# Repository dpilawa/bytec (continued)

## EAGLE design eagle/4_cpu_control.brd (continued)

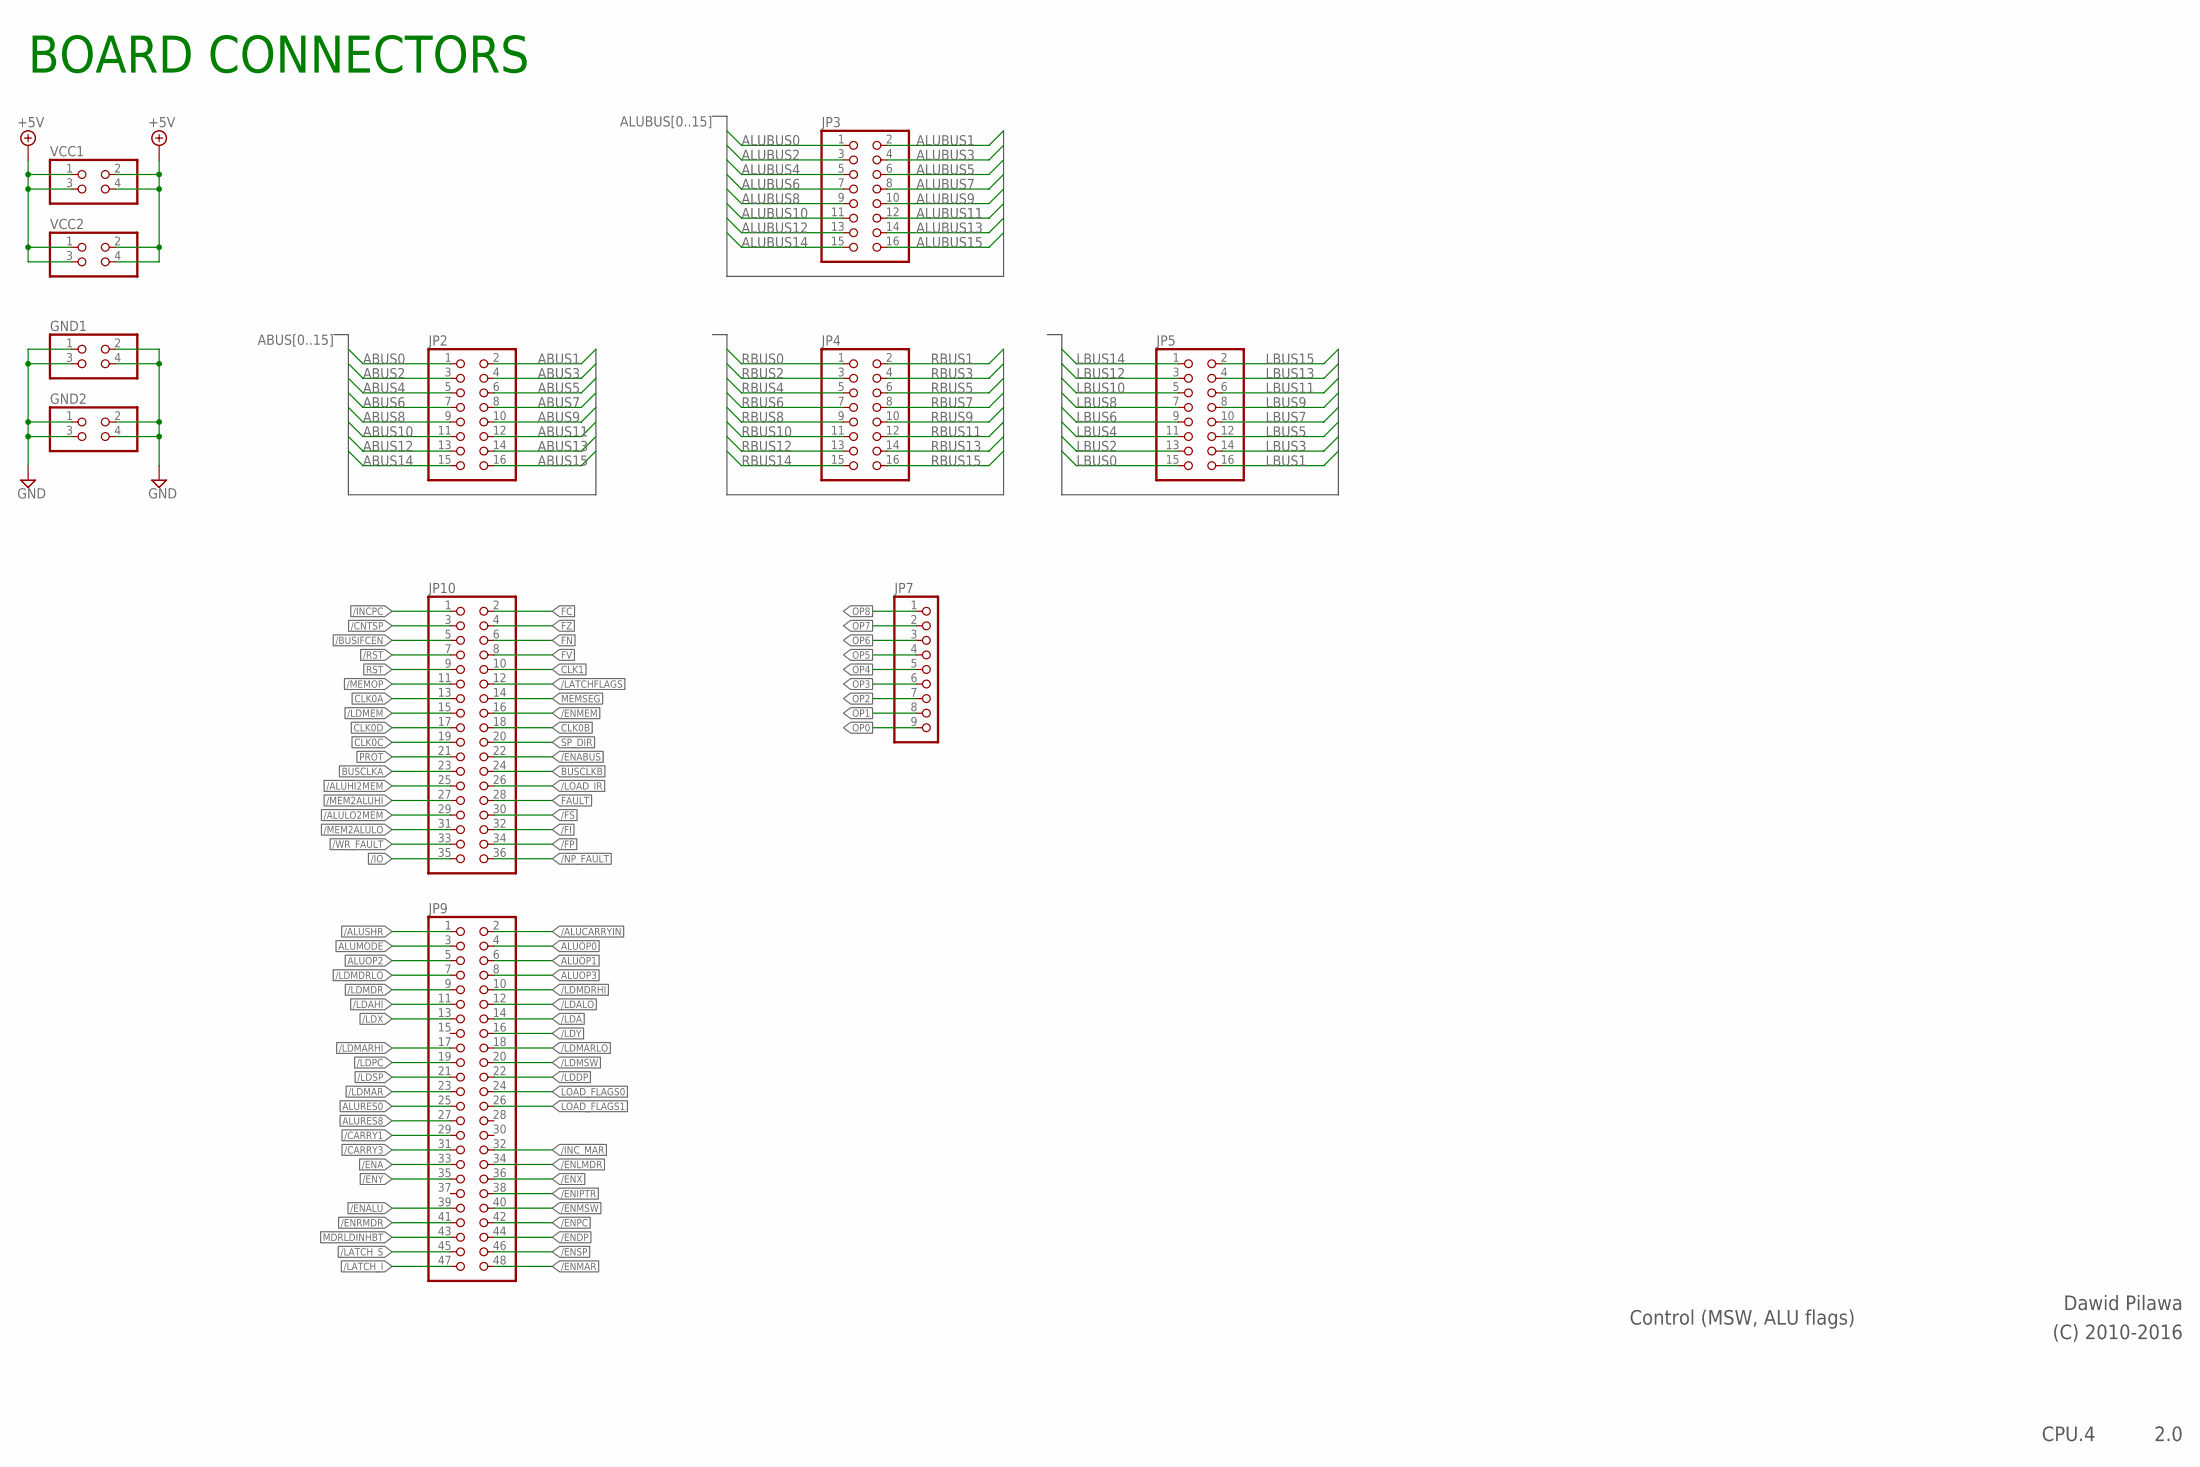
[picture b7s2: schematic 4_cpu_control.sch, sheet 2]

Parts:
GND1, GND2: PINHD-2X2; 2X02
JP2, JP3, JP4, JP5: PINHD-2X8; 2X08
JP7: PINHD-1X9; 1X09
JP9: PINHD-2X24; 2X24
JP10: PINHD-2X18; 2X18
VCC1, VCC2: PINHD-2X2; 2X02

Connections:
+5V: VCC1.1, VCC1.2, VCC1.3, VCC1.4, VCC2.1, VCC2.2, VCC2.3, VCC2.4; also elsewhere on the board
/ALUCARRYIN: JP9.2
/ALUHI2MEM: JP10.25
/ALULO2MEM: JP10.29
/ALUSHR: JP9.1; also elsewhere on the board
/BUSIFCEN: JP10.5
/CARRY1: JP9.29; also elsewhere on the board
/CARRY3: JP9.31; also elsewhere on the board
/CNTSP: JP10.3
/ENA: JP9.33
/ENABUS: JP10.22
/ENALU: JP9.39
/ENDP: JP9.44
/ENIPTR: JP9.38; also elsewhere on the board
/ENLMDR: JP9.34
/ENMAR: JP9.48
/ENMEM: JP10.16
/ENMSW: JP9.40; also elsewhere on the board
/ENPC: JP9.42
/ENRMDR: JP9.41
/ENSP: JP9.46
/ENX: JP9.36
/ENY: JP9.35
/FI: JP10.32; also elsewhere on the board
/FP: JP10.34; also elsewhere on the board
/FS: JP10.30; also elsewhere on the board
/INCPC: JP10.1
/INC_MAR: JP9.32
/IO: JP10.35
/LATCHFLAGS: JP10.12
/LATCH_I: JP9.47; also elsewhere on the board
/LATCH_S: JP9.45; also elsewhere on the board
/LDA: JP9.14
/LDAHI: JP9.11
/LDALO: JP9.12
/LDDP: JP9.22
/LDMAR: JP9.23
/LDMARHI: JP9.17
/LDMARLO: JP9.18
/LDMDR: JP9.9
/LDMDRHI: JP9.10
/LDMDRLO: JP9.7
/LDMEM: JP10.15
/LDMSW: JP9.20; also elsewhere on the board
/LDPC: JP9.19
/LDSP: JP9.21
/LDX: JP9.13
/LDY: JP9.16
/LOAD_IR: JP10.26
/MEM2ALUHI: JP10.27
/MEM2ALULO: JP10.31
/MEMOP: JP10.11
/NP_FAULT: JP10.36
/RST: JP10.7; also elsewhere on the board
/WR_FAULT: JP10.33
ABUS0: JP2.1
ABUS1: JP2.2
ABUS2: JP2.3
ABUS3: JP2.4
ABUS4: JP2.5
ABUS5: JP2.6
ABUS6: JP2.7
ABUS7: JP2.8
ABUS8: JP2.9
ABUS9: JP2.10
ABUS10: JP2.11
ABUS11: JP2.12
ABUS12: JP2.13
ABUS13: JP2.14
ABUS14: JP2.15
ABUS15: JP2.16
ALUBUS0: JP3.1; also elsewhere on the board
ALUBUS1: JP3.2; also elsewhere on the board
ALUBUS2: JP3.3; also elsewhere on the board
ALUBUS3: JP3.4; also elsewhere on the board
ALUBUS4: JP3.5; also elsewhere on the board
ALUBUS5: JP3.6; also elsewhere on the board
ALUBUS6: JP3.7; also elsewhere on the board
ALUBUS7: JP3.8; also elsewhere on the board
ALUBUS8: JP3.9; also elsewhere on the board
ALUBUS9: JP3.10; also elsewhere on the board
ALUBUS10: JP3.11; also elsewhere on the board
ALUBUS11: JP3.12; also elsewhere on the board
ALUBUS12: JP3.13; also elsewhere on the board
ALUBUS13: JP3.14; also elsewhere on the board
ALUBUS14: JP3.15; also elsewhere on the board
ALUBUS15: JP3.16; also elsewhere on the board
ALUMODE: JP9.3
ALUOP0: JP9.4
ALUOP1: JP9.6; also elsewhere on the board
ALUOP2: JP9.5
ALUOP3: JP9.8
ALURES0: JP9.25; also elsewhere on the board
ALURES8: JP9.27; also elsewhere on the board
BUSCLKA: JP10.23
BUSCLKB: JP10.24; also elsewhere on the board
CLK0A: JP10.13
CLK0B: JP10.18
CLK0C: JP10.19
CLK0D: JP10.17; also elsewhere on the board
CLK1: JP10.10
FAULT: JP10.28
FC: JP10.2; also elsewhere on the board
FN: JP10.6; also elsewhere on the board
FV: JP10.8; also elsewhere on the board
FZ: JP10.4; also elsewhere on the board
GND: GND1.1, GND1.2, GND1.3, GND1.4, GND2.1, GND2.2, GND2.3, GND2.4; also elsewhere on the board
LBUS0: JP5.15
LBUS1: JP5.16
LBUS2: JP5.13
LBUS3: JP5.14
LBUS4: JP5.11
LBUS5: JP5.12
LBUS6: JP5.9
LBUS7: JP5.10; also elsewhere on the board
LBUS8: JP5.7
LBUS9: JP5.8
LBUS10: JP5.5
LBUS11: JP5.6
LBUS12: JP5.3
LBUS13: JP5.4
LBUS14: JP5.1
LBUS15: JP5.2; also elsewhere on the board
LOAD_FLAGS0: JP9.24; also elsewhere on the board
LOAD_FLAGS1: JP9.26; also elsewhere on the board
MDRLDINHBT: JP9.43
MEMSEG: JP10.14
OP0: JP7.9; also elsewhere on the board
OP1: JP7.8; also elsewhere on the board
OP2: JP7.7; also elsewhere on the board
OP3: JP7.6; also elsewhere on the board
OP4: JP7.5
OP5: JP7.4
OP6: JP7.3
OP7: JP7.2
OP8: JP7.1
PROT: JP10.21
RBUS0: JP4.1; also elsewhere on the board
RBUS1: JP4.2; also elsewhere on the board
RBUS2: JP4.3; also elsewhere on the board
RBUS3: JP4.4; also elsewhere on the board
RBUS4: JP4.5; also elsewhere on the board
RBUS5: JP4.6; also elsewhere on the board
RBUS6: JP4.7; also elsewhere on the board
RBUS7: JP4.8; also elsewhere on the board
RBUS8: JP4.9; also elsewhere on the board
RBUS9: JP4.10; also elsewhere on the board
RBUS10: JP4.11; also elsewhere on the board
RBUS11: JP4.12; also elsewhere on the board
RBUS12: JP4.13; also elsewhere on the board
RBUS13: JP4.14; also elsewhere on the board
RBUS14: JP4.15; also elsewhere on the board
RBUS15: JP4.16; also elsewhere on the board
RST: JP10.9; also elsewhere on the board
SP_DIR: JP10.20

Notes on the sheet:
Control (MSW, ALU flags)
2.0
Dawid Pilawa
(C) 2010-2016
CPU.4
BOARD CONNECTORS

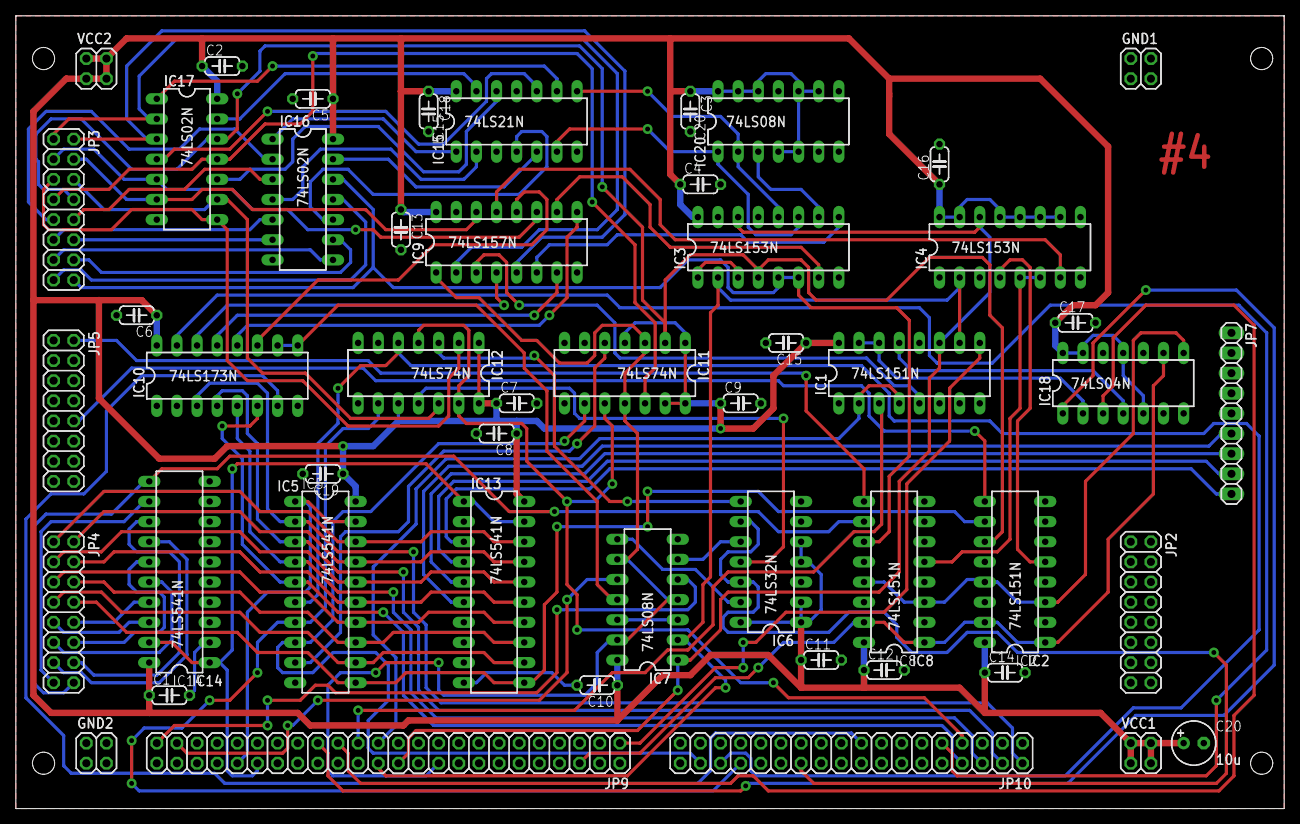
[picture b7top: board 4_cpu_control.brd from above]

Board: 2 copper layers, 160.0 x 100.0 mm, 50 parts (0 on the bottom side), 95 nets.

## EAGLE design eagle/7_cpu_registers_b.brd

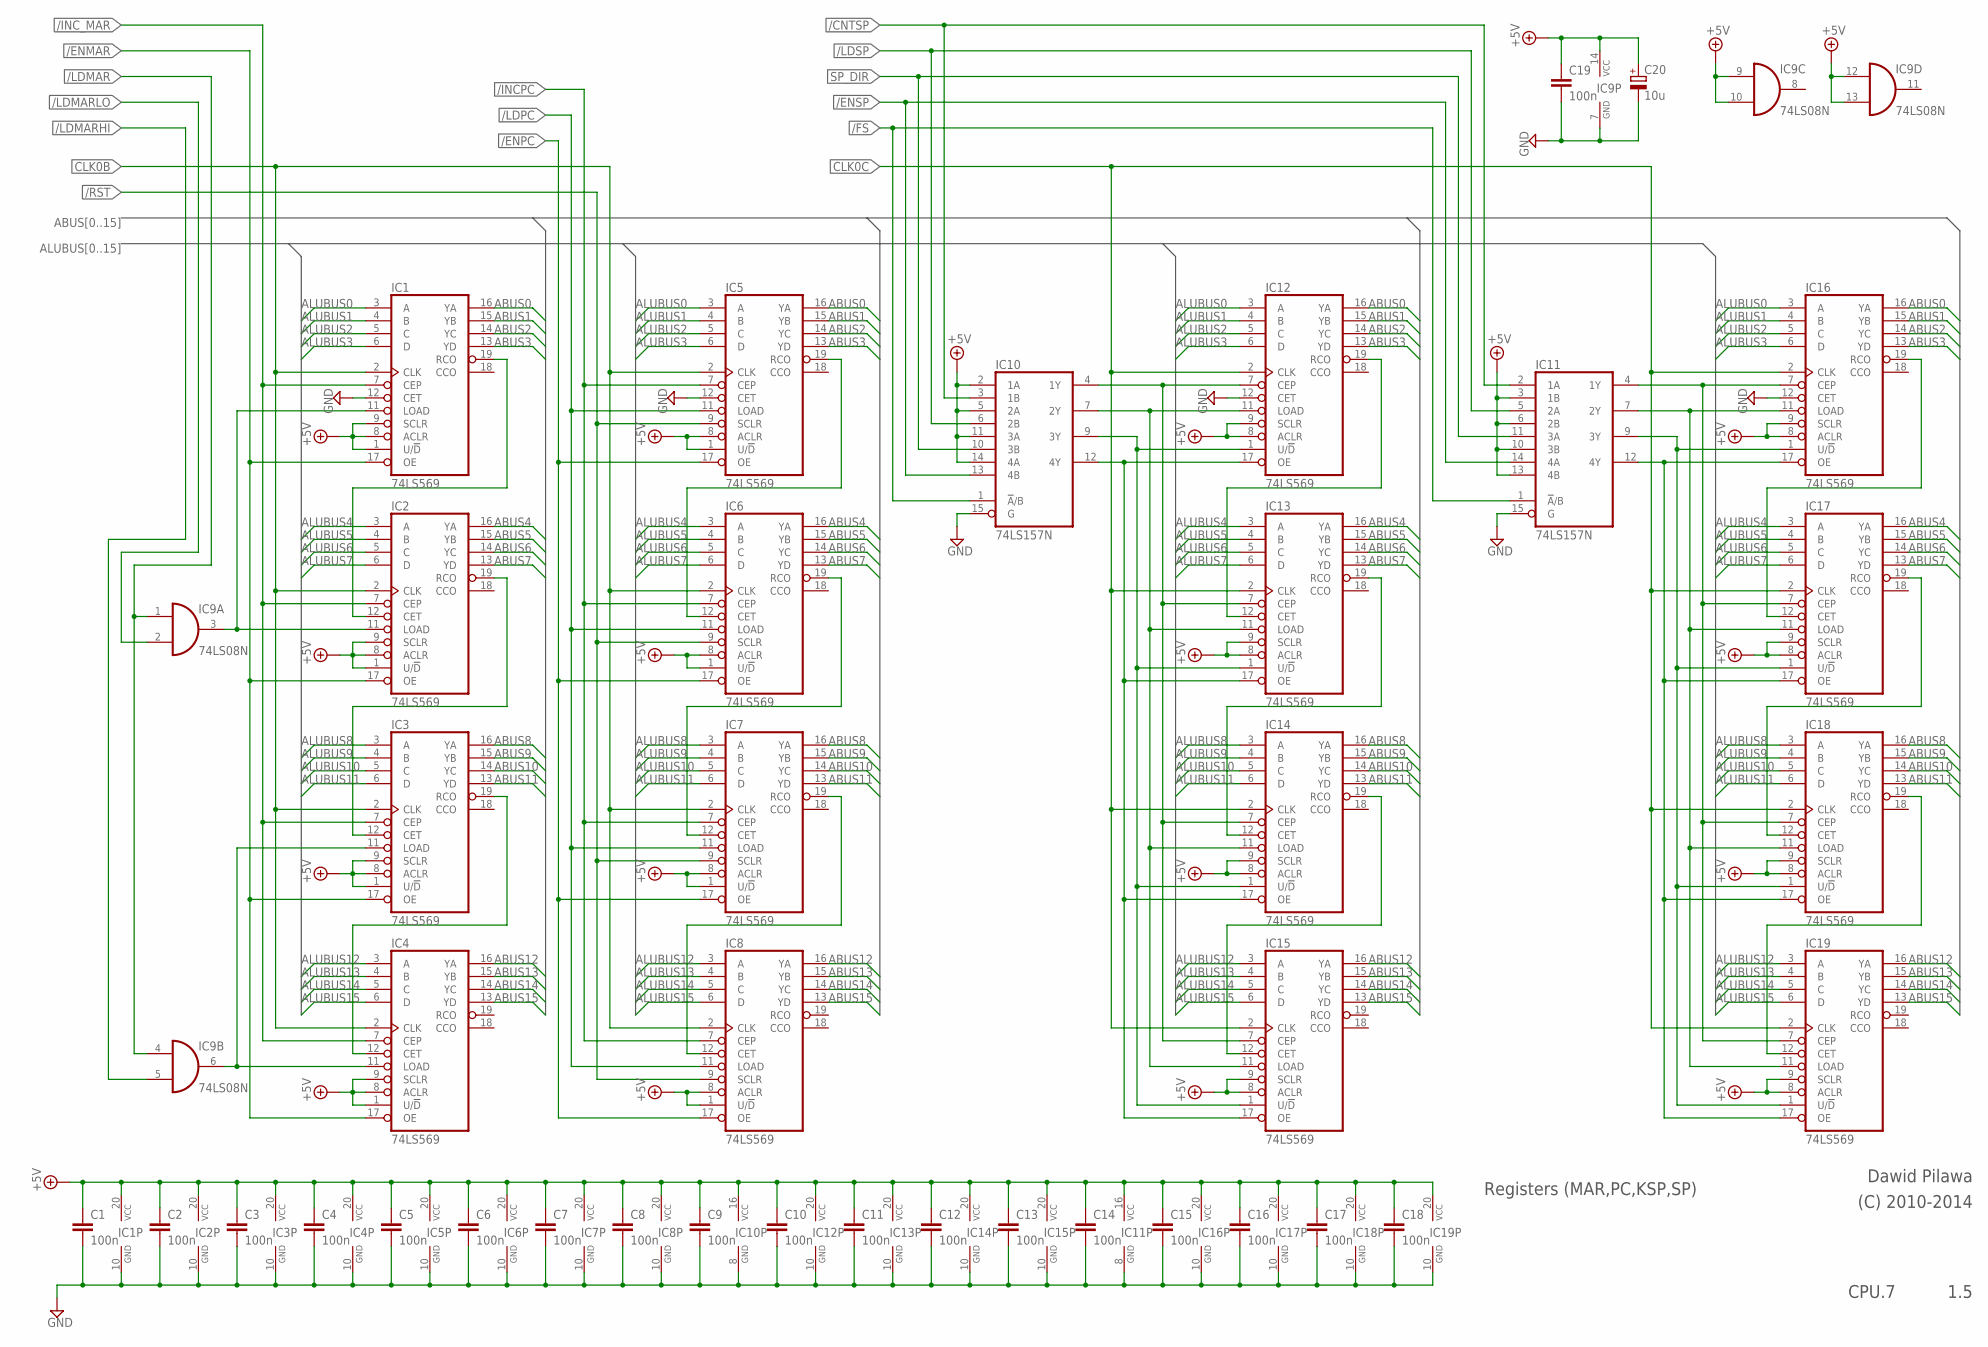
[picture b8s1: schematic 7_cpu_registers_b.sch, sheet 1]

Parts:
C1, C2, C3, C4, C5, C6, C7, C8, C9, C10, C11, C12, C13, C14, C15, C16, C17, C18, C19: 100n; C050-024X044
C20: 10u; E2,5-6
IC1, IC2, IC3, IC4, IC5, IC6, IC7, IC8, IC12, IC13, IC14, IC15, IC16, IC17, IC18, IC19: 74LS569; DIL20
IC9: 74LS08N; DIL14
IC10, IC11: 74LS157N; DIL16

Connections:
+5V: C1.1, C2.1, C3.1, C4.1, C5.1, C6.1, C7.1, C8.1, C9.1, C10.1, C11.1, C12.1, C13.1, C14.1, C15.1, C16.1, C17.1, C18.1, C19.1, C20.+, IC1.1 (U/!D), IC1.8 (ACLR), IC1.9 (SCLR), IC1.20 (VCC), IC2.1 (U/!D), IC2.8 (ACLR), IC2.9 (SCLR), IC2.20 (VCC), IC3.1 (U/!D), IC3.8 (ACLR), IC3.9 (SCLR), IC3.20 (VCC), IC4.1 (U/!D), IC4.8 (ACLR), IC4.9 (SCLR), IC4.20 (VCC), IC5.1 (U/!D), IC5.8 (ACLR), IC5.20 (VCC), IC6.1 (U/!D), IC6.8 (ACLR), IC6.20 (VCC), IC7.1 (U/!D), IC7.8 (ACLR), IC7.20 (VCC), IC8.1 (U/!D), IC8.8 (ACLR), IC8.20 (VCC), IC9.9 (I0), IC9.10 (I1), IC9.12 (I0), IC9.13 (I1), IC9.14 (VCC), IC10.2 (1A), IC10.5 (2A), IC10.11 (3A), IC10.14 (4A), IC10.16 (VCC), IC11.3 (1B), IC11.6 (2B), IC11.10 (3B), IC11.13 (4B), IC11.16 (VCC), IC12.8 (ACLR), IC12.9 (SCLR), IC12.20 (VCC), IC13.8 (ACLR), IC13.9 (SCLR), IC13.20 (VCC), IC14.8 (ACLR), IC14.9 (SCLR), IC14.20 (VCC), IC15.8 (ACLR), IC15.9 (SCLR), IC15.20 (VCC), IC16.8 (ACLR), IC16.9 (SCLR), IC16.20 (VCC), IC17.8 (ACLR), IC17.9 (SCLR), IC17.20 (VCC), IC18.8 (ACLR), IC18.9 (SCLR), IC18.20 (VCC), IC19.8 (ACLR), IC19.9 (SCLR), IC19.20 (VCC); also elsewhere on the board
/CNTSP: IC10.3 (1B), IC11.2 (1A); also elsewhere on the board
/ENMAR: IC1.17 (OE), IC2.17 (OE), IC3.17 (OE), IC4.17 (OE); also elsewhere on the board
/ENPC: IC5.17 (OE), IC6.17 (OE), IC7.17 (OE), IC8.17 (OE); also elsewhere on the board
/ENSP: IC10.13 (4B), IC11.14 (4A); also elsewhere on the board
/FS: IC10.1 (!A!/B), IC11.1 (!A!/B); also elsewhere on the board
/INCPC: IC5.7 (CEP), IC6.7 (CEP), IC7.7 (CEP), IC8.7 (CEP); also elsewhere on the board
/INC_MAR: IC1.7 (CEP), IC2.7 (CEP), IC3.7 (CEP), IC4.7 (CEP); also elsewhere on the board
/LDMAR: IC9.1 (I0), IC9.4 (I0); also elsewhere on the board
/LDMARHI: IC9.5 (I1); also elsewhere on the board
/LDMARLO: IC9.2 (I1); also elsewhere on the board
/LDPC: IC5.11 (LOAD), IC6.11 (LOAD), IC7.11 (LOAD), IC8.11 (LOAD); also elsewhere on the board
/LDSP: IC10.6 (2B), IC11.5 (2A); also elsewhere on the board
/RST: IC5.9 (SCLR), IC6.9 (SCLR), IC7.9 (SCLR), IC8.9 (SCLR); also elsewhere on the board
ABUS0: IC1.16 (YA), IC5.16 (YA), IC12.16 (YA), IC16.16 (YA); also elsewhere on the board
ABUS1: IC1.15 (YB), IC5.15 (YB), IC12.15 (YB), IC16.15 (YB); also elsewhere on the board
ABUS2: IC1.14 (YC), IC5.14 (YC), IC12.14 (YC), IC16.14 (YC); also elsewhere on the board
ABUS3: IC1.13 (YD), IC5.13 (YD), IC12.13 (YD), IC16.13 (YD); also elsewhere on the board
ABUS4: IC2.16 (YA), IC6.16 (YA), IC13.16 (YA), IC17.16 (YA); also elsewhere on the board
ABUS5: IC2.15 (YB), IC6.15 (YB), IC13.15 (YB), IC17.15 (YB); also elsewhere on the board
ABUS6: IC2.14 (YC), IC6.14 (YC), IC13.14 (YC), IC17.14 (YC); also elsewhere on the board
ABUS7: IC2.13 (YD), IC6.13 (YD), IC13.13 (YD), IC17.13 (YD); also elsewhere on the board
ABUS8: IC3.16 (YA), IC7.16 (YA), IC14.16 (YA), IC18.16 (YA); also elsewhere on the board
ABUS9: IC3.15 (YB), IC7.15 (YB), IC14.15 (YB), IC18.15 (YB); also elsewhere on the board
ABUS10: IC3.14 (YC), IC7.14 (YC), IC14.14 (YC), IC18.14 (YC); also elsewhere on the board
ABUS11: IC3.13 (YD), IC7.13 (YD), IC14.13 (YD), IC18.13 (YD); also elsewhere on the board
ABUS12: IC4.16 (YA), IC8.16 (YA), IC15.16 (YA), IC19.16 (YA); also elsewhere on the board
ABUS13: IC4.15 (YB), IC8.15 (YB), IC15.15 (YB), IC19.15 (YB); also elsewhere on the board
ABUS14: IC4.14 (YC), IC8.14 (YC), IC15.14 (YC), IC19.14 (YC); also elsewhere on the board
ABUS15: IC4.13 (YD), IC8.13 (YD), IC15.13 (YD), IC19.13 (YD); also elsewhere on the board
ALUBUS0: IC1.3 (A), IC5.3 (A), IC12.3 (A), IC16.3 (A); also elsewhere on the board
ALUBUS1: IC1.4 (B), IC5.4 (B), IC12.4 (B), IC16.4 (B); also elsewhere on the board
ALUBUS2: IC1.5 (C), IC5.5 (C), IC12.5 (C), IC16.5 (C); also elsewhere on the board
ALUBUS3: IC1.6 (D), IC5.6 (D), IC12.6 (D), IC16.6 (D); also elsewhere on the board
ALUBUS4: IC2.3 (A), IC6.3 (A), IC13.3 (A), IC17.3 (A); also elsewhere on the board
ALUBUS5: IC2.4 (B), IC6.4 (B), IC13.4 (B), IC17.4 (B); also elsewhere on the board
ALUBUS6: IC2.5 (C), IC6.5 (C), IC13.5 (C), IC17.5 (C); also elsewhere on the board
ALUBUS7: IC2.6 (D), IC6.6 (D), IC13.6 (D), IC17.6 (D); also elsewhere on the board
ALUBUS8: IC3.3 (A), IC7.3 (A), IC14.3 (A), IC18.3 (A); also elsewhere on the board
ALUBUS9: IC3.4 (B), IC7.4 (B), IC14.4 (B), IC18.4 (B); also elsewhere on the board
ALUBUS10: IC3.5 (C), IC7.5 (C), IC14.5 (C), IC18.5 (C); also elsewhere on the board
ALUBUS11: IC3.6 (D), IC7.6 (D), IC14.6 (D), IC18.6 (D); also elsewhere on the board
ALUBUS12: IC4.3 (A), IC8.3 (A), IC15.3 (A), IC19.3 (A); also elsewhere on the board
ALUBUS13: IC4.4 (B), IC8.4 (B), IC15.4 (B), IC19.4 (B); also elsewhere on the board
ALUBUS14: IC4.5 (C), IC8.5 (C), IC15.5 (C), IC19.5 (C); also elsewhere on the board
ALUBUS15: IC4.6 (D), IC8.6 (D), IC15.6 (D), IC19.6 (D); also elsewhere on the board
CLK0B: IC1.2 (CLK), IC2.2 (CLK), IC3.2 (CLK), IC4.2 (CLK), IC5.2 (CLK), IC6.2 (CLK), IC7.2 (CLK), IC8.2 (CLK); also elsewhere on the board
CLK0C: IC12.2 (CLK), IC13.2 (CLK), IC14.2 (CLK), IC15.2 (CLK), IC16.2 (CLK), IC17.2 (CLK), IC18.2 (CLK), IC19.2 (CLK); also elsewhere on the board
GND: C1.2, C2.2, C3.2, C4.2, C5.2, C6.2, C7.2, C8.2, C9.2, C10.2, C11.2, C12.2, C13.2, C14.2, C15.2, C16.2, C17.2, C18.2, C19.2, C20.-, IC1.10 (GND), IC1.12 (CET), IC2.10 (GND), IC3.10 (GND), IC4.10 (GND), IC5.10 (GND), IC5.12 (CET), IC6.10 (GND), IC7.10 (GND), IC8.10 (GND), IC9.7 (GND), IC10.8 (GND), IC10.15 (G), IC11.8 (GND), IC11.15 (G), IC12.10 (GND), IC12.12 (CET), IC13.10 (GND), IC14.10 (GND), IC15.10 (GND), IC16.10 (GND), IC16.12 (CET), IC17.10 (GND), IC18.10 (GND), IC19.10 (GND); also elsewhere on the board
unnamed: IC1.11 (LOAD), IC2.11 (LOAD), IC9.3 (O)
unnamed: IC6.19 (RCO), IC7.12 (CET)
unnamed: IC5.19 (RCO), IC6.12 (CET)
unnamed: IC7.19 (RCO), IC8.12 (CET)
unnamed: IC12.19 (RCO), IC13.12 (CET)
unnamed: IC13.19 (RCO), IC14.12 (CET)
unnamed: IC3.11 (LOAD), IC4.11 (LOAD), IC9.6 (O)
unnamed: IC14.19 (RCO), IC15.12 (CET)
unnamed: IC10.4 (1Y), IC12.7 (CEP), IC13.7 (CEP), IC14.7 (CEP), IC15.7 (CEP)
unnamed: IC1.19 (RCO), IC2.12 (CET)
unnamed: IC2.19 (RCO), IC3.12 (CET)
unnamed: IC3.19 (RCO), IC4.12 (CET)
unnamed: IC10.7 (2Y), IC12.11 (LOAD), IC13.11 (LOAD), IC14.11 (LOAD), IC15.11 (LOAD)
unnamed: IC10.9 (3Y), IC12.1 (U/!D), IC13.1 (U/!D), IC14.1 (U/!D), IC15.1 (U/!D)
unnamed: IC11.9 (3Y), IC16.1 (U/!D), IC17.1 (U/!D), IC18.1 (U/!D), IC19.1 (U/!D)
unnamed: IC10.12 (4Y), IC12.17 (OE), IC13.17 (OE), IC14.17 (OE), IC15.17 (OE)
unnamed: IC11.12 (4Y), IC16.17 (OE), IC17.17 (OE), IC18.17 (OE), IC19.17 (OE)
unnamed: IC16.19 (RCO), IC17.12 (CET)
unnamed: IC17.19 (RCO), IC18.12 (CET)
unnamed: IC18.19 (RCO), IC19.12 (CET)
unnamed: IC11.4 (1Y), IC16.7 (CEP), IC17.7 (CEP), IC18.7 (CEP), IC19.7 (CEP)
unnamed: IC11.7 (2Y), IC16.11 (LOAD), IC17.11 (LOAD), IC18.11 (LOAD), IC19.11 (LOAD)
SP_DIR: IC10.10 (3B), IC11.11 (3A); also elsewhere on the board

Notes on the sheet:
Registers (MAR,PC,KSP,SP)
Dawid Pilawa
(C) 2010-2014
CPU.7
1.5

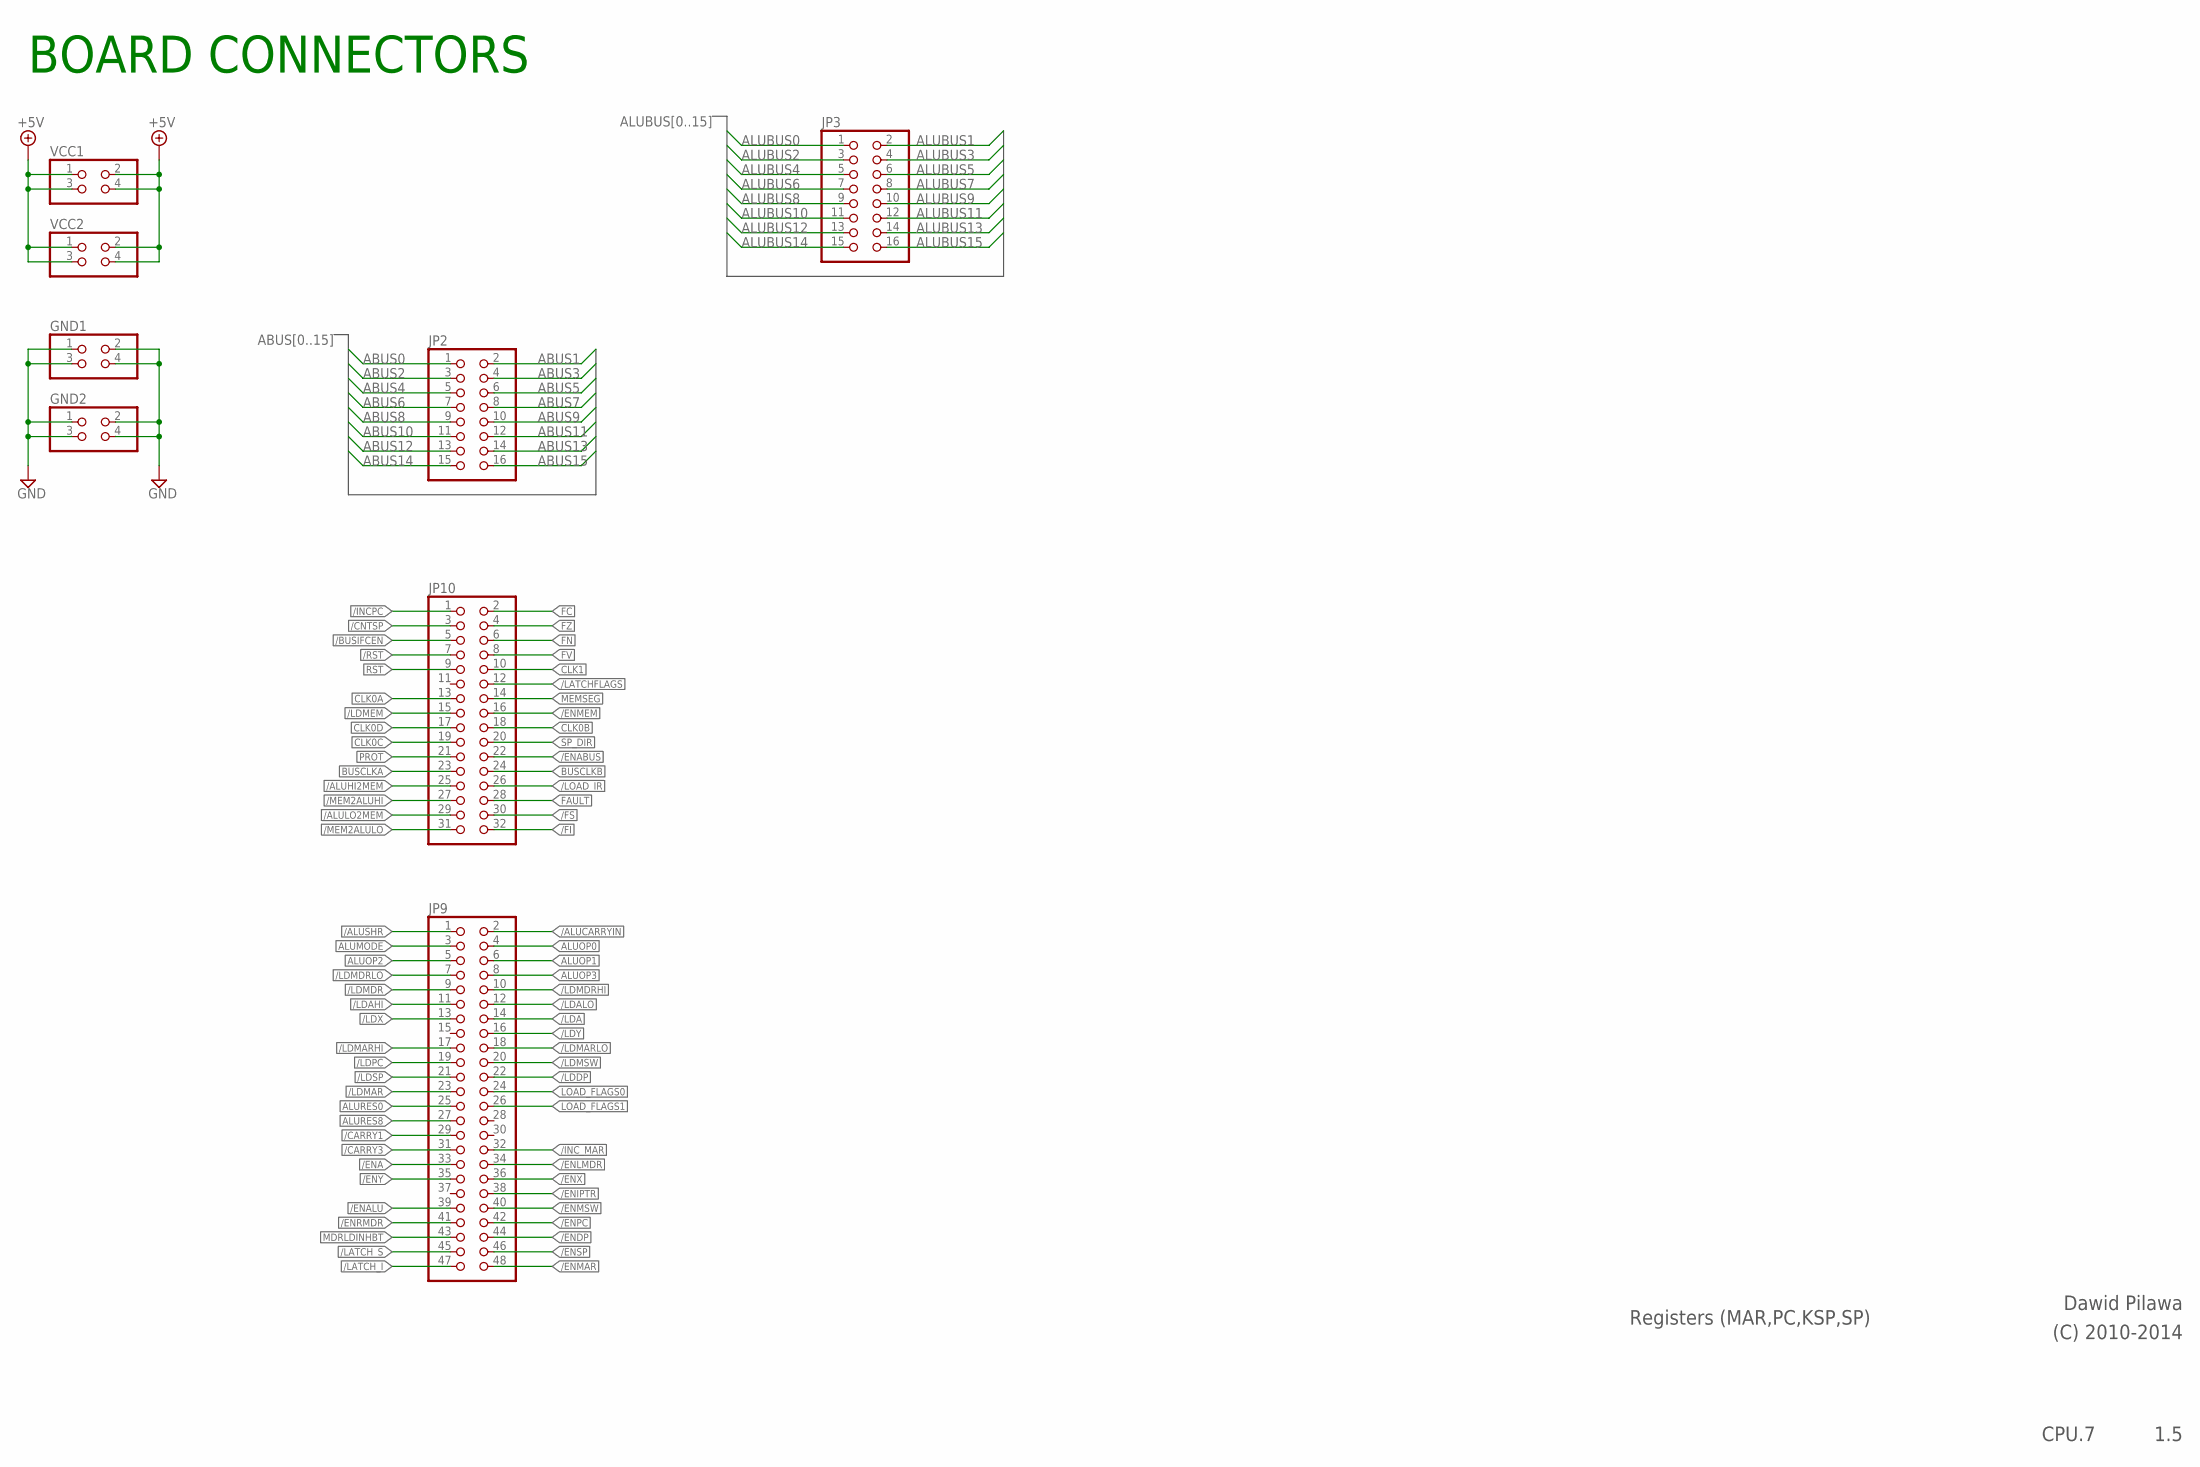
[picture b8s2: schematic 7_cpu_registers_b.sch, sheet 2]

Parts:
GND1, GND2: PINHD-2X2; 2X02
JP2, JP3: PINHD-2X8; 2X08
JP9: PINHD-2X24; 2X24
JP10: PINHD-2X16; 2X16
VCC1, VCC2: PINHD-2X2; 2X02

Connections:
+5V: VCC1.1, VCC1.2, VCC1.3, VCC1.4, VCC2.1, VCC2.2, VCC2.3, VCC2.4; also elsewhere on the board
/ALUCARRYIN: JP9.2
/ALUHI2MEM: JP10.25
/ALULO2MEM: JP10.29
/ALUSHR: JP9.1
/BUSIFCEN: JP10.5
/CARRY1: JP9.29
/CARRY3: JP9.31
/CNTSP: JP10.3; also elsewhere on the board
/ENA: JP9.33
/ENABUS: JP10.22
/ENALU: JP9.39
/ENDP: JP9.44
/ENIPTR: JP9.38
/ENLMDR: JP9.34
/ENMAR: JP9.48; also elsewhere on the board
/ENMEM: JP10.16
/ENMSW: JP9.40
/ENPC: JP9.42; also elsewhere on the board
/ENRMDR: JP9.41
/ENSP: JP9.46; also elsewhere on the board
/ENX: JP9.36
/ENY: JP9.35
/FI: JP10.32
/FP: JP10.34
/FS: JP10.30; also elsewhere on the board
/INCPC: JP10.1; also elsewhere on the board
/INC_MAR: JP9.32; also elsewhere on the board
/IO: JP10.35
/LATCHFLAGS: JP10.12
/LATCH_I: JP9.47
/LATCH_S: JP9.45
/LDA: JP9.14
/LDAHI: JP9.11
/LDALO: JP9.12
/LDDP: JP9.22
/LDMAR: JP9.23; also elsewhere on the board
/LDMARHI: JP9.17; also elsewhere on the board
/LDMARLO: JP9.18; also elsewhere on the board
/LDMDR: JP9.9
/LDMDRHI: JP9.10
/LDMDRLO: JP9.7
/LDMEM: JP10.15
/LDMSW: JP9.20
/LDPC: JP9.19; also elsewhere on the board
/LDSP: JP9.21; also elsewhere on the board
/LDX: JP9.13
/LDY: JP9.16
/LOAD_IR: JP10.26
/MEM2ALUHI: JP10.27
/MEM2ALULO: JP10.31
/MEMOP: JP10.11
/NP_FAULT: JP10.36
/RST: JP10.7; also elsewhere on the board
/WR_FAULT: JP10.33
ABUS0: JP2.1; also elsewhere on the board
ABUS1: JP2.2; also elsewhere on the board
ABUS2: JP2.3; also elsewhere on the board
ABUS3: JP2.4; also elsewhere on the board
ABUS4: JP2.5; also elsewhere on the board
ABUS5: JP2.6; also elsewhere on the board
ABUS6: JP2.7; also elsewhere on the board
ABUS7: JP2.8; also elsewhere on the board
ABUS8: JP2.9; also elsewhere on the board
ABUS9: JP2.10; also elsewhere on the board
ABUS10: JP2.11; also elsewhere on the board
ABUS11: JP2.12; also elsewhere on the board
ABUS12: JP2.13; also elsewhere on the board
ABUS13: JP2.14; also elsewhere on the board
ABUS14: JP2.15; also elsewhere on the board
ABUS15: JP2.16; also elsewhere on the board
ALUBUS0: JP3.1; also elsewhere on the board
ALUBUS1: JP3.2; also elsewhere on the board
ALUBUS2: JP3.3; also elsewhere on the board
ALUBUS3: JP3.4; also elsewhere on the board
ALUBUS4: JP3.5; also elsewhere on the board
ALUBUS5: JP3.6; also elsewhere on the board
ALUBUS6: JP3.7; also elsewhere on the board
ALUBUS7: JP3.8; also elsewhere on the board
ALUBUS8: JP3.9; also elsewhere on the board
ALUBUS9: JP3.10; also elsewhere on the board
ALUBUS10: JP3.11; also elsewhere on the board
ALUBUS11: JP3.12; also elsewhere on the board
ALUBUS12: JP3.13; also elsewhere on the board
ALUBUS13: JP3.14; also elsewhere on the board
ALUBUS14: JP3.15; also elsewhere on the board
ALUBUS15: JP3.16; also elsewhere on the board
ALUMODE: JP9.3
ALUOP0: JP9.4
ALUOP1: JP9.6
ALUOP2: JP9.5
ALUOP3: JP9.8
ALURES0: JP9.25
ALURES8: JP9.27
BUSCLKA: JP10.23
BUSCLKB: JP10.24
CLK0A: JP10.13
CLK0B: JP10.18; also elsewhere on the board
CLK0C: JP10.19; also elsewhere on the board
CLK0D: JP10.17
CLK1: JP10.10
FAULT: JP10.28
FC: JP10.2
FN: JP10.6
FV: JP10.8
FZ: JP10.4
GND: GND1.1, GND1.2, GND1.3, GND1.4, GND2.1, GND2.2, GND2.3, GND2.4; also elsewhere on the board
LOAD_FLAGS0: JP9.24
LOAD_FLAGS1: JP9.26
MDRLDINHBT: JP9.43
MEMSEG: JP10.14
PROT: JP10.21
RST: JP10.9
SP_DIR: JP10.20; also elsewhere on the board

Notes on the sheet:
Registers (MAR,PC,KSP,SP)
Dawid Pilawa
(C) 2010-2014
CPU.7
1.5
BOARD CONNECTORS

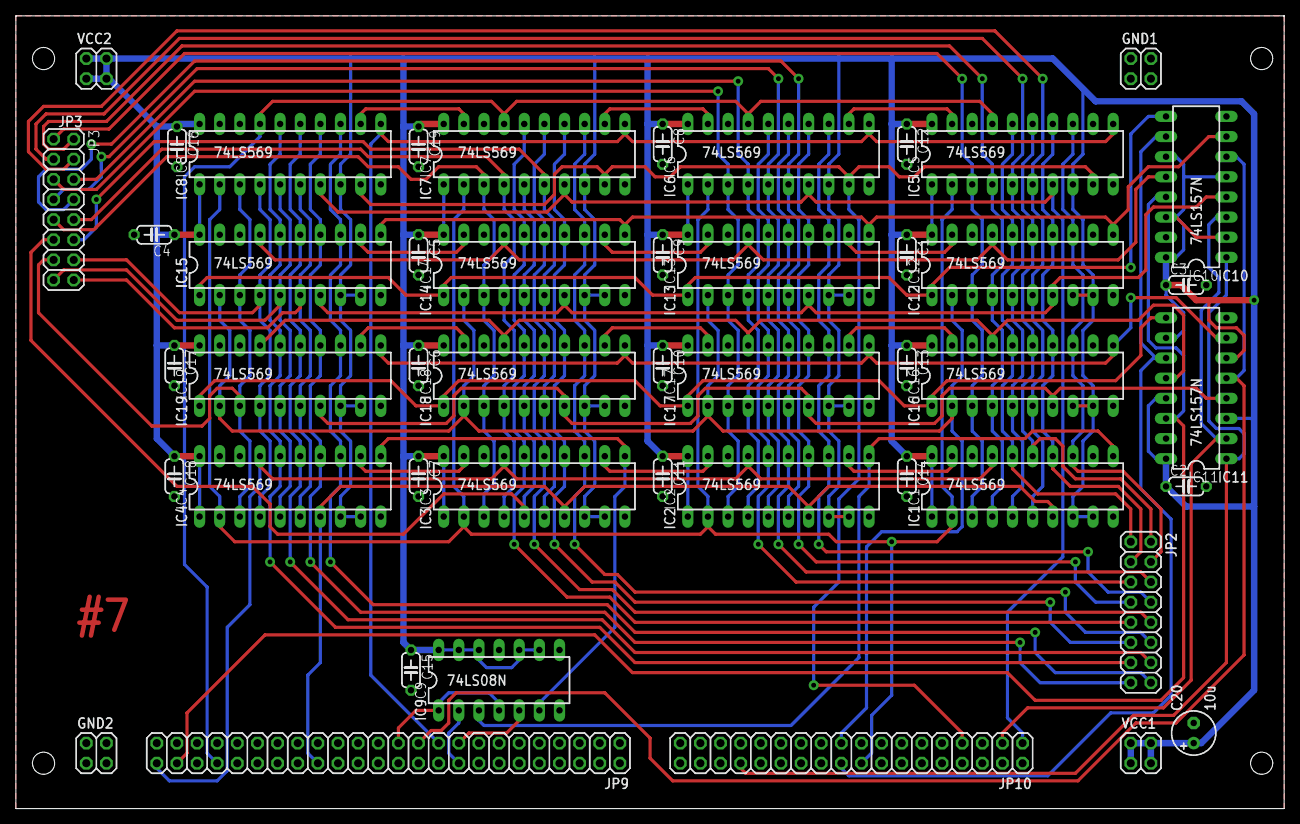
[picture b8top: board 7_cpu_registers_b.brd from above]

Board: 2 copper layers, 160.0 x 100.0 mm, 47 parts (0 on the bottom side), 72 nets.

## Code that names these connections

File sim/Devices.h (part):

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{
    void go(long t) {} ;
public:
    IRQ(std::string label, Wire& irq0, Wire& irq1, Wire& irq2, Wire& irq3, Wire& irq4, Wire& irq5, Wire& irq6, Wire& irq7);
    void go(int irq, long time, int s_len);
};

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{
    Logic lq1, lq2, lq1_bar, lq2_bar;   
public:
    LS74(std::string label, Wire& clk1, Wire& clk2, Wire& pr1_bar, Wire& pr2_bar, Wire& clr1_bar, Wire& clr2_bar, 
        Wire& d1, Wire& d2, Wire& q1, Wire& q2, Wire& q1_bar, Wire& q2_bar);
    void go(long t);
    void debugInfo() {};
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
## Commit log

2015-12-21 Removed lcc variants
2015-12-21 Removed excess files
2015-12-28 Renamed F6 to /FP
2015-12-28 Added /FP (flag paging enabled) to schematics and board, extended header connector
2015-12-31 All boards prepared for MMU extension
2015-12-31 Removed obsolete power connector board
2015-12-31 remove .appledouble folders from repo
2016-01-06 Parts library updated (added fast SRAM), MMU board half complete
2016-01-12 MMU schematics update
2016-01-12 Eagle project file update
2016-01-13 Updates to MMU faults generation circuit
2016-01-13 Removed obsolete binary files from gate-level simulator
2016-01-20 More MMU changes, added PPREG
2016-01-22 Removal of PPC started
2016-01-24 PPC removal completed, control card RBUS selector changed from LS138 to LS139, removed /LDPPC and /ENPPC signals
2016-01-24 Renumbered boards and schematic sheets
2016-01-28 Updated ucasm for CPU 2.0. Added IRET and MEMOP signals, reduced RBUS field size to 2 bits and removed PPC enable signal.
2016-01-28 Modified CPU diagram
2016-01-28 Removed remaining references to PPC in ucasm
2016-01-28 Updated microcode for v2.0 of the CPU
2016-02-06 Sat Feb 6 20:10:54 CET 2016
2016-02-08 UCasm: renamed IRET to FRET (fault return) and modified microcode word layout to match new schematics
2016-02-08 Mon Feb 8 16:27:58 CET 2016
2016-02-09 2016-02-09 13:30
2016-02-09 2016-02-09 18:12
2016-02-10 2016-02-10 17:30 (completed boards 2,6,7)
2016-02-10 Wed Feb 10 21:42:14 CET 2016
2016-02-10 Wed Feb 10 22:17:37 CET 2016 (completed boards 5,4)
2016-02-10 Completed board 3
2016-02-11 Fixed microcode word layout, updated microcode (added FRET in place of HALT)
2016-02-11 Removed eagle.epf from tracking
2016-02-11 Completed board 0
2016-02-15 MMU board in progress
2016-02-16 MMU schematics completed
2016-02-16 MMU power rails and bypass caps added in schematic, board started
2016-02-20 Cosmetic change to board 2
2016-02-22 MMU board layout updates
2016-02-24 MMU board updates 2016-02-24
2016-02-25 MMU board updates 2016-02-25
2016-03-04 MMU and Memory board updates, removed mem_ext board (obsolete)
2016-03-07 Memory board v2.0 completed
2016-03-08 Gerber files added for Memory Board (v2.0)
2016-03-16 MMU board updates 2016-03-16
2016-03-24 MMU board updates 2016-03-24
2016-04-14 MMU board updates 2016-04-13
2016-04-14 MMU board completed
2016-04-14 Library update to CPU board #0, addedd schematics PDFs
2016-04-15 Updates for CPU rev.2.0 release
2016-04-15 Removed obsolete files
2016-04-15 Removed obsolete files cont.
2019-01-07 added .gitignore
2019-03-24 assembler changes for cpu rev. 2.0
2023-12-12 fault opcodes now store MDR and MAR
2023-12-12 added supervisor protection for IRET and FRET
